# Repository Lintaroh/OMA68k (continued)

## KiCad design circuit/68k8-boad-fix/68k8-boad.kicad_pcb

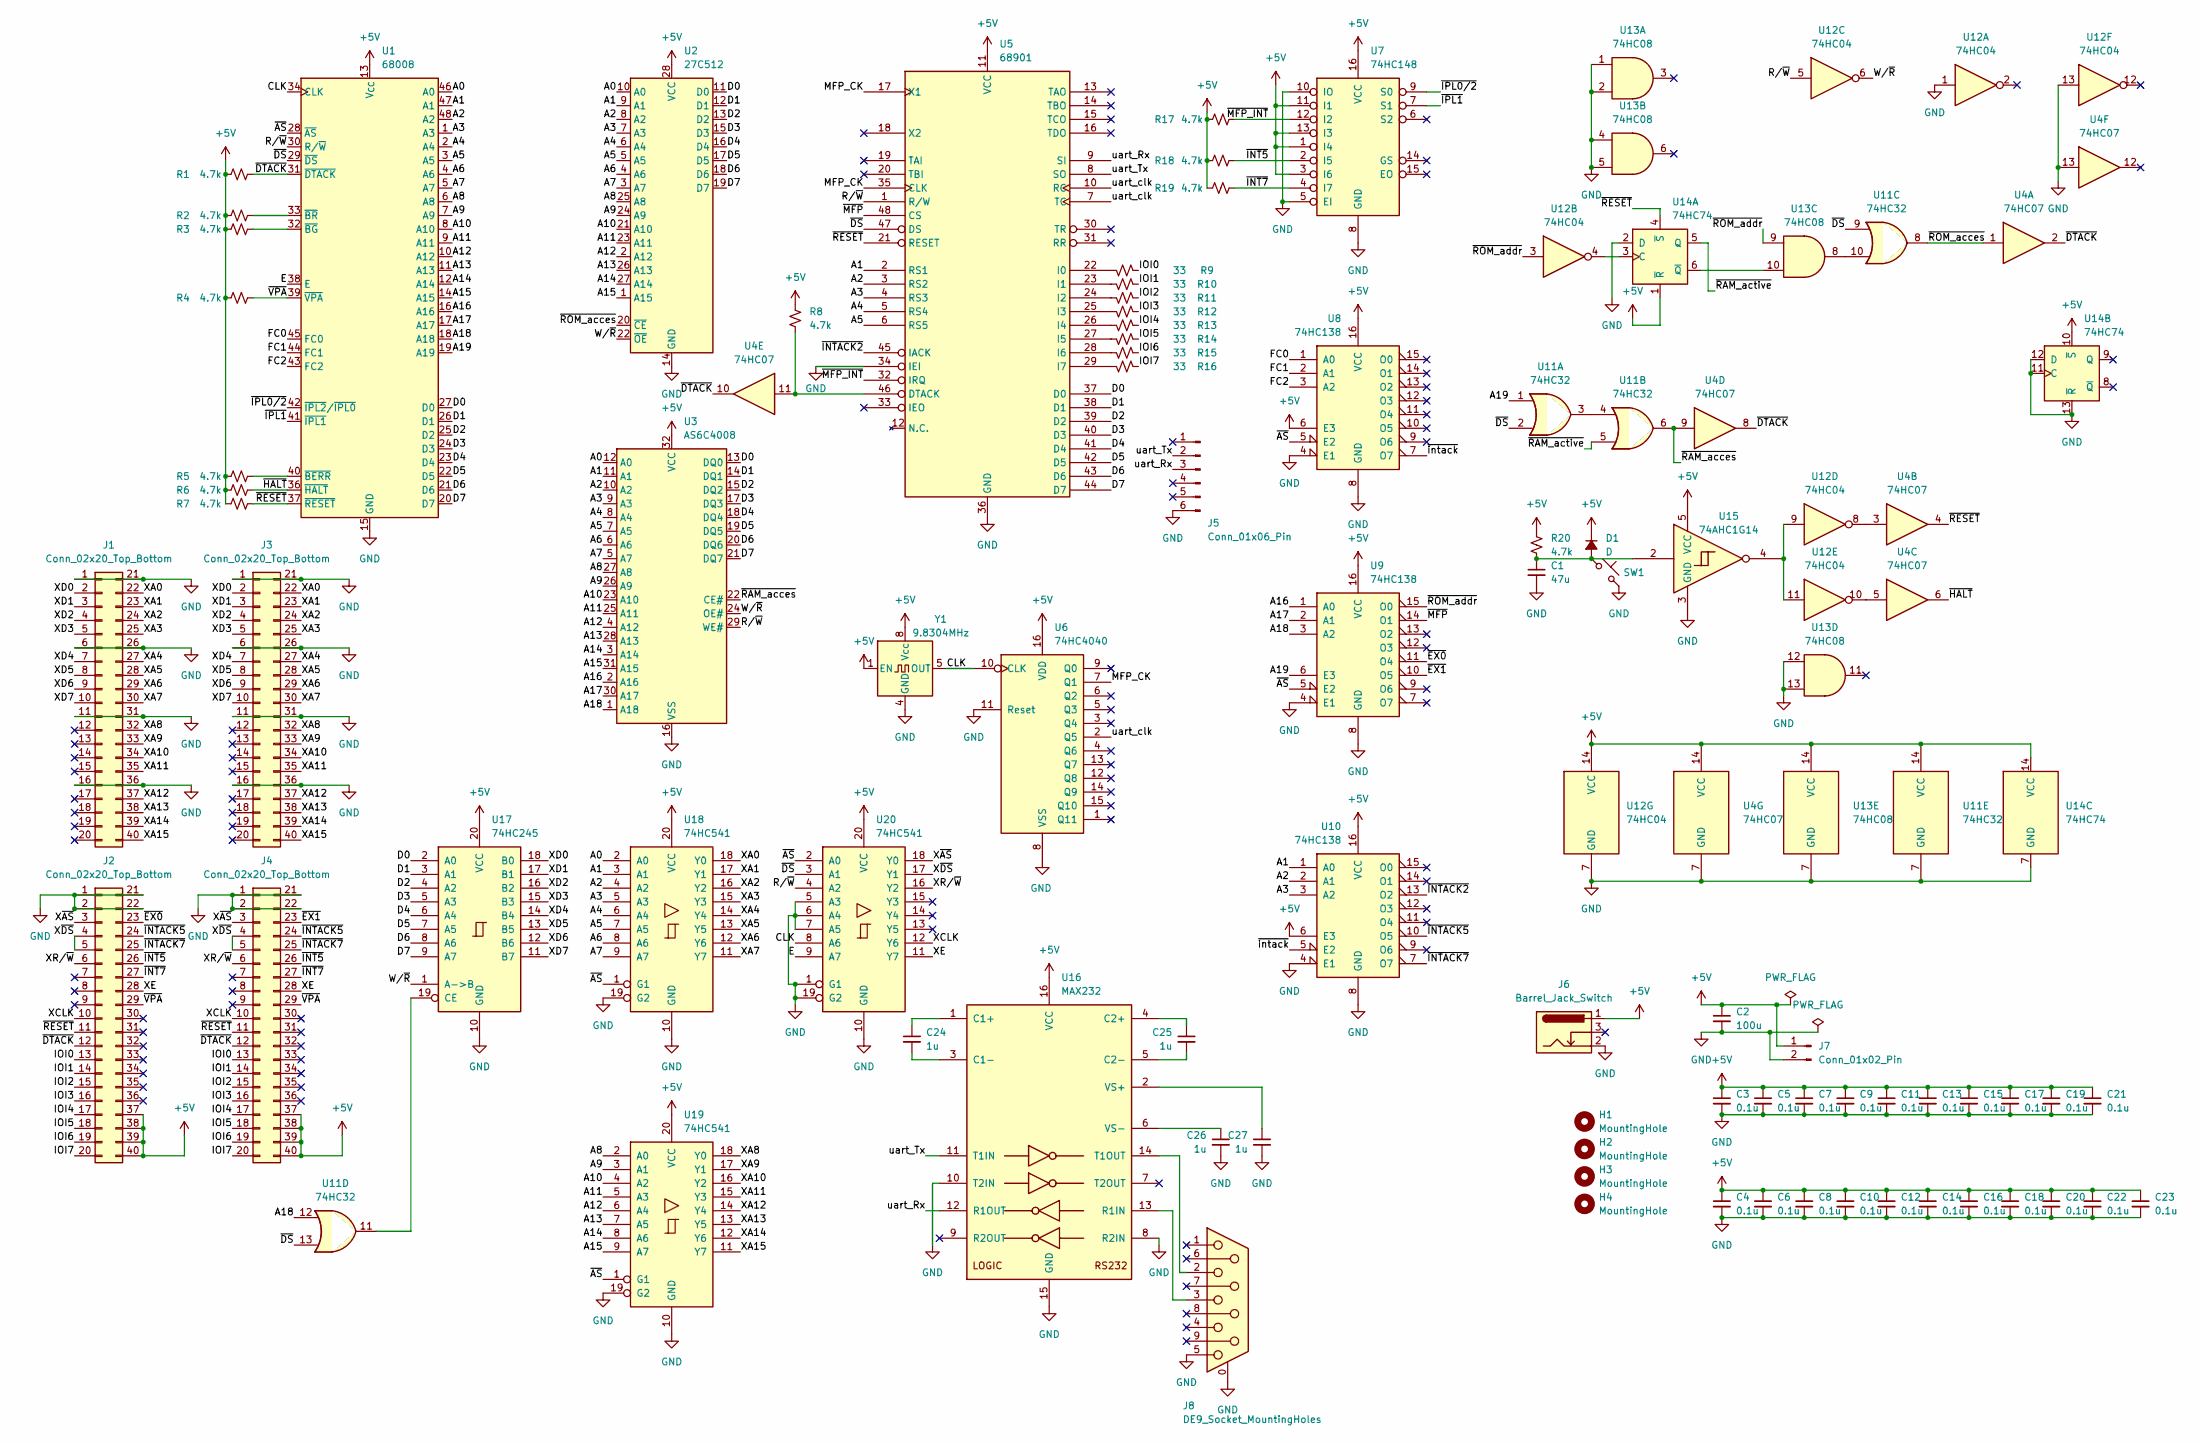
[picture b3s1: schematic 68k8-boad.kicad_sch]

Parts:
C1: 47u; CP_Radial_D5.0mm_P2.50mm
C2: 100u; CP_Radial_D6.3mm_P2.50mm
C3, C4, C5, C6, C7, C8, C9, C10, C11, C12, C13, C14, C15, C16, C17, C18, C19, C20, C21, C22, C23: 0.1u; C_Disc_D4.3mm_W1.9mm_P5.00mm
C24, C25, C26, C27: 1u; C_0805_2012Metric
D1: D; D_DO-34_SOD68_P7.62mm_Horizontal
H1, H2, H3, H4: MountingHole; MountingHole_3.2mm_M3
J1, J2, J3, J4: Conn_02x20_Top_Bottom; PinSocket_2x20_P2.54mm_Vertical
J5: Conn_01x06_Pin; PinHeader_1x06_P2.54mm_Vertical
J6: Barrel_Jack_Switch; BarrelJack_Horizontal
J7: Conn_01x02_Pin; JST_EH_B2B-EH-A_1x02_P2.50mm_Vertical
J8: DE9_Socket_MountingHoles; DSUB-9_Socket_Horizontal_P2.77x2.84mm_EdgePinOffset7.70mm_H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
R1, R2, R3, R4, R5, R6, R7, R8, R17, R18, R19, R20: 4.7k; R_0603_1608Metric
R9, R10, R11, R12, R13, R14, R15, R16: 33; R_0603_1608Metric
SW1: SW_PUSH_6mm_H5mm
U1: 68008; DIP-48_W15.24mm
U2: 27C512; DIP-28_W15.24mm
U3: AS6C4008; DIP-32_W15.24mm
U4: 74HC07; DIP-14_W7.62mm
U5: 68901; DIP-48_W15.24mm
U6: 74HC4040; DIP-16_W7.62mm
U7: 74HC148; DIP-16_W7.62mm
U8, U9, U10: 74HC138; DIP-16_W7.62mm
U11: 74HC32; DIP-14_W7.62mm
U12: 74HC04; DIP-14_W7.62mm
U13: 74HC08; DIP-14_W7.62mm
U14: 74HC74; DIP-14_W7.62mm
U15: 74AHC1G14; SOT-23-5
U16: MAX232; DIP-16_W7.62mm
U17: 74HC245; DIP-20_W7.62mm
U18, U19, U20: 74HC541; DIP-20_W7.62mm
Y1: 9.8304MHz; Oscillator_DIP-8

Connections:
+5V: C2.1, C3.1, C4.1, C5.1, C6.1, C7.1, C8.1, C9.1, C10.1, C11.1, C12.1, C13.1, C14.1, C15.1, C16.1, C17.1, C18.1, C19.1, C20.1, C21.1, C22.1, C23.1, D1.1 (K), J2.37, J2.38, J2.39, J2.40, J4.37, J4.38, J4.39, J4.40, J6.1, J7.1, R1.1, R2.1, R3.1, R4.1, R5.1, R6.1, R7.1, R8.1, R17.1, R18.1, R19.1, R20.1, U1.13 (V_{CC}), U2.28 (VCC), U3.32 (VCC), U4.14 (VCC), U5.11 (VCC), U6.16 (VDD), U7.1 (I4), U7.3 (I6), U7.11 (I1), U7.13 (I3), U7.16 (VCC), U8.6 (E3), U8.16 (VCC), U9.16 (VCC), U10.6 (E3), U10.16 (VCC), U11.14 (VCC), U12.14 (VCC), U13.14 (VCC), U14.1 (~R), U14.10 (~S), U14.14 (VCC), U15.5 (VCC), U16.16 (VCC), U17.20 (VCC), U18.20 (VCC), U19.20 (VCC), U20.20 (VCC), Y1.1 (EN), Y1.8 (Vcc)
/A0: U1.46 (A0), U2.10 (A0), U3.12 (A0), U18.2 (A0)
/A1: U1.47 (A1), U2.9 (A1), U3.11 (A1), U5.2 (RS1), U10.1 (A0), U18.3 (A1)
/A2: U1.48 (A2), U2.8 (A2), U3.10 (A2), U5.3 (RS2), U10.2 (A1), U18.4 (A2)
/A3: U1.1 (A3), U2.7 (A3), U3.9 (A3), U5.4 (RS3), U10.3 (A2), U18.5 (A3)
/A4: U1.2 (A4), U2.6 (A4), U3.8 (A4), U5.5 (RS4), U18.6 (A4)
/A5: U1.3 (A5), U2.5 (A5), U3.7 (A5), U5.6 (RS5), U18.7 (A5)
/A6: U1.4 (A6), U2.4 (A6), U3.6 (A6), U18.8 (A6)
/A7: U1.5 (A7), U2.3 (A7), U3.5 (A7), U18.9 (A7)
/A8: U1.6 (A8), U2.25 (A8), U3.27 (A8), U19.2 (A0)
/A9: U1.7 (A9), U2.24 (A9), U3.26 (A9), U19.3 (A1)
/A10: U1.8 (A10), U2.21 (A10), U3.23 (A10), U19.4 (A2)
/A11: U1.9 (A11), U2.23 (A11), U3.25 (A11), U19.5 (A3)
/A12: U1.10 (A12), U2.2 (A12), U3.4 (A12), U19.6 (A4)
/A13: U1.11 (A13), U2.26 (A13), U3.28 (A13), U19.7 (A5)
/A14: U1.12 (A14), U2.27 (A14), U3.3 (A14), U19.8 (A6)
/A15: U1.14 (A15), U2.1 (A15), U3.31 (A15), U19.9 (A7)
/A16: U1.16 (A16), U3.2 (A16), U9.1 (A0)
/A17: U1.17 (A17), U3.30 (A17), U9.2 (A1)
/A18: U1.18 (A18), U3.1 (A18), U9.3 (A2), U11.12
/A19: U1.19 (A19), U9.6 (E3), U11.1
/CLK: U1.34 (CLK), U6.10 (CLK), U20.8 (A6), Y1.5 (OUT)
/D0: U1.27 (D0), U2.11 (D0), U3.13 (DQ0), U5.37 (D0), U17.2 (A0)
/D1: U1.26 (D1), U2.12 (D1), U3.14 (DQ1), U5.38 (D1), U17.3 (A1)
/D2: U1.25 (D2), U2.13 (D2), U3.15 (DQ2), U5.39 (D2), U17.4 (A2)
/D3: U1.24 (D3), U2.15 (D3), U3.17 (DQ3), U5.40 (D3), U17.5 (A3)
/D4: U1.23 (D4), U2.16 (D4), U3.18 (DQ4), U5.41 (D4), U17.6 (A4)
/D5: U1.22 (D5), U2.17 (D5), U3.19 (DQ5), U5.42 (D5), U17.7 (A5)
/D6: U1.21 (D6), U2.18 (D6), U3.20 (DQ6), U5.43 (D6), U17.8 (A6)
/D7: U1.20 (D7), U2.19 (D7), U3.21 (DQ7), U5.44 (D7), U17.9 (A7)
/E: U1.38 (E), U20.9 (A7)
/FC0: U1.45 (FC0), U8.1 (A0)
/FC1: U1.44 (FC1), U8.2 (A1)
/FC2: U1.43 (FC2), U8.3 (A2)
/IOI0: J2.13, J4.13, R9.1
/IOI1: J2.14, J4.14, R10.1
/IOI2: J2.15, J4.15, R11.1
/IOI3: J2.16, J4.16, R12.1
/IOI4: J2.17, J4.17, R13.1
/IOI5: J2.18, J4.18, R14.1
/IOI6: J2.19, J4.19, R15.1
/IOI7: J2.20, J4.20, R16.1
/MFP_CK: U5.17 (X1), U5.35 (CLK), U6.7 (Q1)
/R/~W: U1.30 (R/~W), U3.29 (WE#), U5.1 (R/W), U12.5, U20.4 (A2)
/W/~R: U2.22 (~OE), U3.24 (OE#), U12.6, U17.1 (A->B)
/XA0: J1.22, J3.22, U18.18 (Y0)
/XA1: J1.23, J3.23, U18.17 (Y1)
/XA2: J1.24, J3.24, U18.16 (Y2)
/XA3: J1.25, J3.25, U18.15 (Y3)
/XA4: J1.27, J3.27, U18.14 (Y4)
/XA5: J1.28, J3.28, U18.13 (Y5)
/XA6: J1.29, J3.29, U18.12 (Y6)
/XA7: J1.30, J3.30, U18.11 (Y7)
/XA8: J1.32, J3.32, U19.18 (Y0)
/XA9: J1.33, J3.33, U19.17 (Y1)
/XA10: J1.34, J3.34, U19.16 (Y2)
/XA11: J1.35, J3.35, U19.15 (Y3)
/XA12: J1.37, J3.37, U19.14 (Y4)
/XA13: J1.38, J3.38, U19.13 (Y5)
/XA14: J1.39, J3.39, U19.12 (Y6)
/XA15: J1.40, J3.40, U19.11 (Y7)
/XCLK: J2.10, J4.10, U20.12 (Y6)
/XD0: J1.2, J3.2, U17.18 (B0)
/XD1: J1.3, J3.3, U17.17 (B1)
/XD2: J1.4, J3.4, U17.16 (B2)
/XD3: J1.5, J3.5, U17.15 (B3)
/XD4: J1.7, J3.7, U17.14 (B4)
/XD5: J1.8, J3.8, U17.13 (B5)
/XD6: J1.9, J3.9, U17.12 (B6)
/XD7: J1.10, J3.10, U17.11 (B7)
/XE: J2.28, J4.28, U20.11 (Y7)
/XR/~W: J2.6, J4.6, U20.16 (Y2)
/X~AS: J2.3, J4.3, U20.18 (Y0)
/X~DS: J2.4, J2.5, J4.4, J4.5, U20.17 (Y1)
/uart_Rx: J5.3, U5.9 (SI), U16.12 (R1OUT)
/uart_Tx: J5.2, U5.8 (SO), U16.11 (T1IN)
/uart_clk: U5.7 (TC), U5.10 (RC), U6.2 (Q5)
/~AS: U1.28 (~AS), U8.5 (E2), U9.5 (E2), U18.1 (G1), U19.1 (G1), U20.2 (A0)
/~DS: U1.29 (~DS), U5.47 (DS), U11.2, U11.9, U11.13, U20.3 (A1)
/~DTACK: J2.12, J4.12, R1.2, U1.31 (~DTACK), U4.2, U4.8, U4.10
/~EX0: J2.23, U9.11 (O4)
/~EX1: J4.23, U9.10 (O5)
/~HALT: R6.2, U1.36 (~HALT), U4.6
/~INT5: J2.26, J4.26, R18.2, U7.2 (I5)
/~INT7: J2.27, J4.27, R19.2, U7.4 (I7)
/~INTACK2: U5.45 (IACK), U10.13 (O2)
/~INTACK5: J2.24, J4.24, U10.10 (O5)
/~INTACK7: J2.25, J4.25, U10.7 (O7)
/~IPL0/2: U1.42 (~IPL2/~IPL0), U7.9 (S0)
/~IPL1: U1.41 (~IPL1), U7.7 (S1)
/~MFP_INT: R17.2, U5.32 (IRQ), U7.12 (I2)
/~MFP: U5.48 (CS), U9.14 (O1)
/~RAM_acces: U3.22 (CE#), U4.9, U11.6
/~RAM_active: U11.5, U14.5 (Q)
/~RESET: J2.11, J4.11, R7.2, U1.37 (~RESET), U4.4, U5.21 (RESET), U14.4 (~S)
/~ROM_acces: U2.20 (~CE), U4.1, U11.8
/~ROM_addr: U9.15 (O0), U12.3, U13.9
/~VPA: J2.29, J4.29, R4.2, U1.39 (~VPA)
/~intack: U8.7 (O7), U10.5 (E2)
GND: C1.2, C2.2, C3.2, C4.2, C5.2, C6.2, C7.2, C8.2, C9.2, C10.2, C11.2, C12.2, C13.2, C14.2, C15.2, C16.2, C17.2, C18.2, C19.2, C20.2, C21.2, C22.2, C23.2, C26.2, C27.2, J1.1, J1.6, J1.11, J1.16, J1.21, J1.26, J1.31, J1.36, J2.1, J2.2, J2.21, J2.22, J3.1, J3.6, J3.11, J3.16, J3.21, J3.26, J3.31, J3.36, J4.1, J4.2, J4.21, J4.22, J5.6, J6.2, J7.2, J8.0 (PAD), J8.5, SW1.2, U1.15 (GND), U1.35 (GND), U2.14 (GND), U3.16 (VSS), U4.7 (GND), U4.13, U5.34 (IEI), U5.36 (GND), U6.8 (VSS), U6.11 (Reset), U7.5 (EI), U7.8 (GND), U7.10 (IO), U8.4 (E1), U8.8 (GND), U9.4 (E1), U9.8 (GND), U10.4 (E1), U10.8 (GND), U11.7 (GND), U12.1, U12.7 (GND), U12.13, U13.1, U13.2, U13.4, U13.5, U13.7 (GND), U13.12, U13.13, U14.2 (D), U14.7 (GND), U14.11 (C), U14.12 (D), U14.13 (~R), U15.3 (GND), U16.8 (R2IN), U16.10 (T2IN), U16.15 (GND), U17.10 (GND), U18.10 (GND), U18.19 (G2), U19.10 (GND), U19.19 (G2), U20.1 (G1), U20.5 (A3), U20.6 (A4), U20.7 (A5), U20.10 (GND), U20.19 (G2), Y1.4 (GND)
unnamed: C1.1, D1.2 (A), R20.2, SW1.1, U15.2
unnamed: R5.2, U1.40 (~BERR)
unnamed: R3.2, U1.32 (~BG)
unnamed: R2.2, U1.33 (~BR)
unnamed: R8.2, U4.11, U5.46 (DTACK)
unnamed: R9.2, U5.22 (I0)
unnamed: R10.2, U5.23 (I1)
unnamed: R11.2, U5.24 (I2)
unnamed: R12.2, U5.25 (I3)
unnamed: R13.2, U5.26 (I4)
unnamed: R14.2, U5.27 (I5)
unnamed: R15.2, U5.28 (I6)
unnamed: R16.2, U5.29 (I7)
unnamed: U11.3, U11.4
unnamed: U11.10, U13.8
unnamed: U4.3, U12.8
unnamed: U4.5, U12.10
unnamed: U12.9, U12.11, U15.4
unnamed: U12.4, U14.3 (C)
unnamed: U13.10, U14.6 (~Q)
unnamed: C24.1, U16.1 (C1+)
unnamed: C24.2, U16.3 (C1-)
unnamed: C25.1, U16.4 (C2+)
unnamed: C25.2, U16.5 (C2-)
unnamed: J8.3, U16.13 (R1IN)
unnamed: J8.2, U16.14 (T1OUT)
unnamed: C27.1, U16.2 (VS+)
unnamed: C26.1, U16.6 (VS-)
unnamed: U11.11, U17.19 (CE)

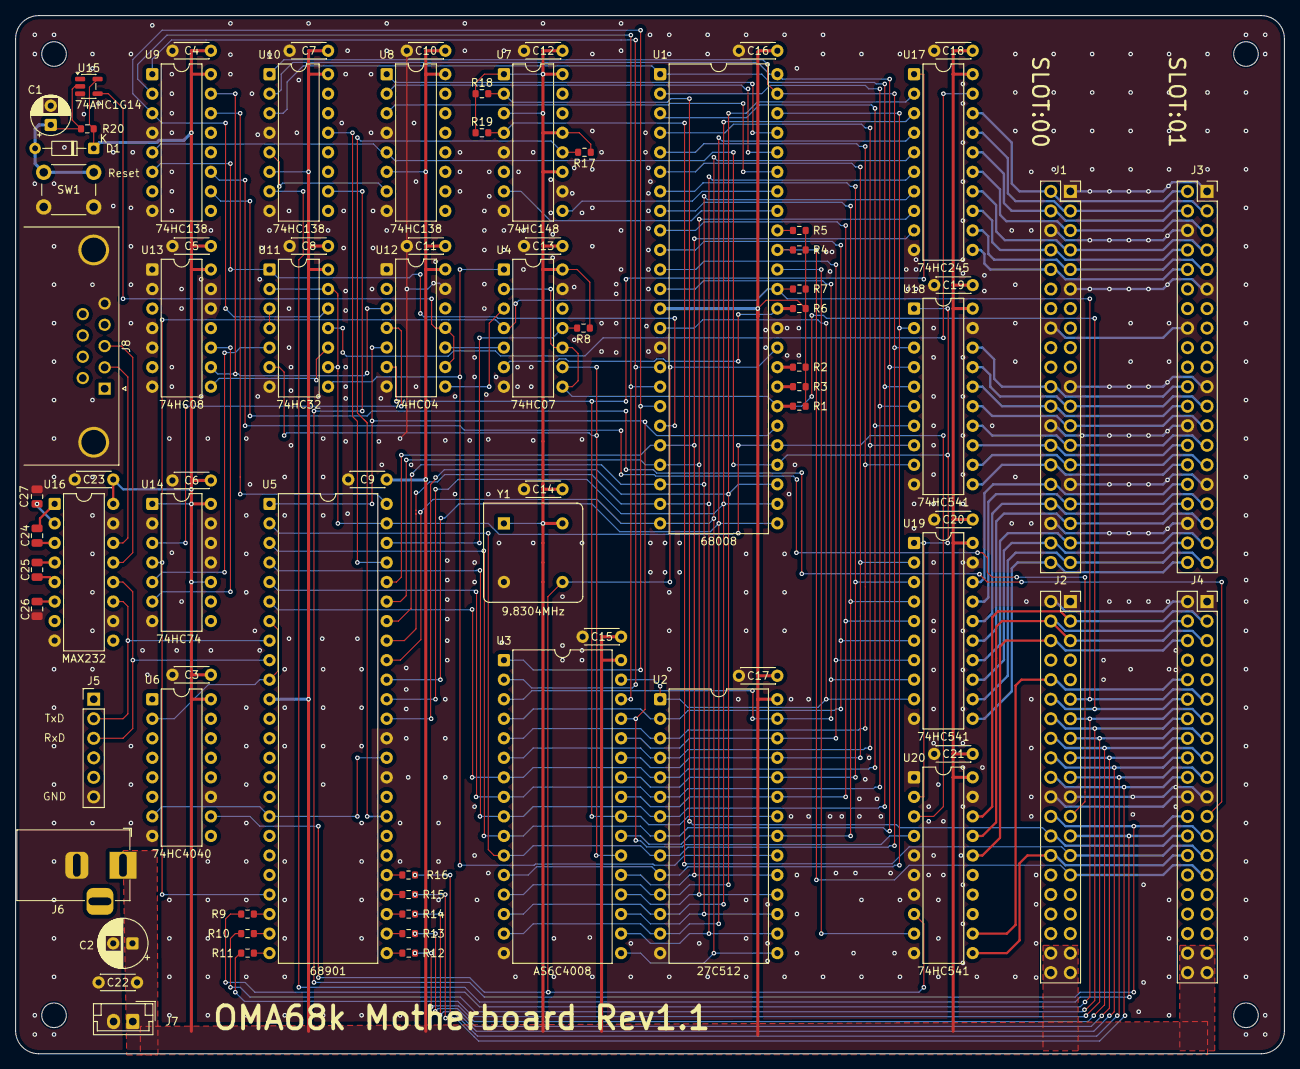
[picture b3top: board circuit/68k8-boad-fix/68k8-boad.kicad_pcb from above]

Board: 2 copper layers, 165.0 x 135.0 mm, 82 parts (0 on the bottom side), 129 nets.

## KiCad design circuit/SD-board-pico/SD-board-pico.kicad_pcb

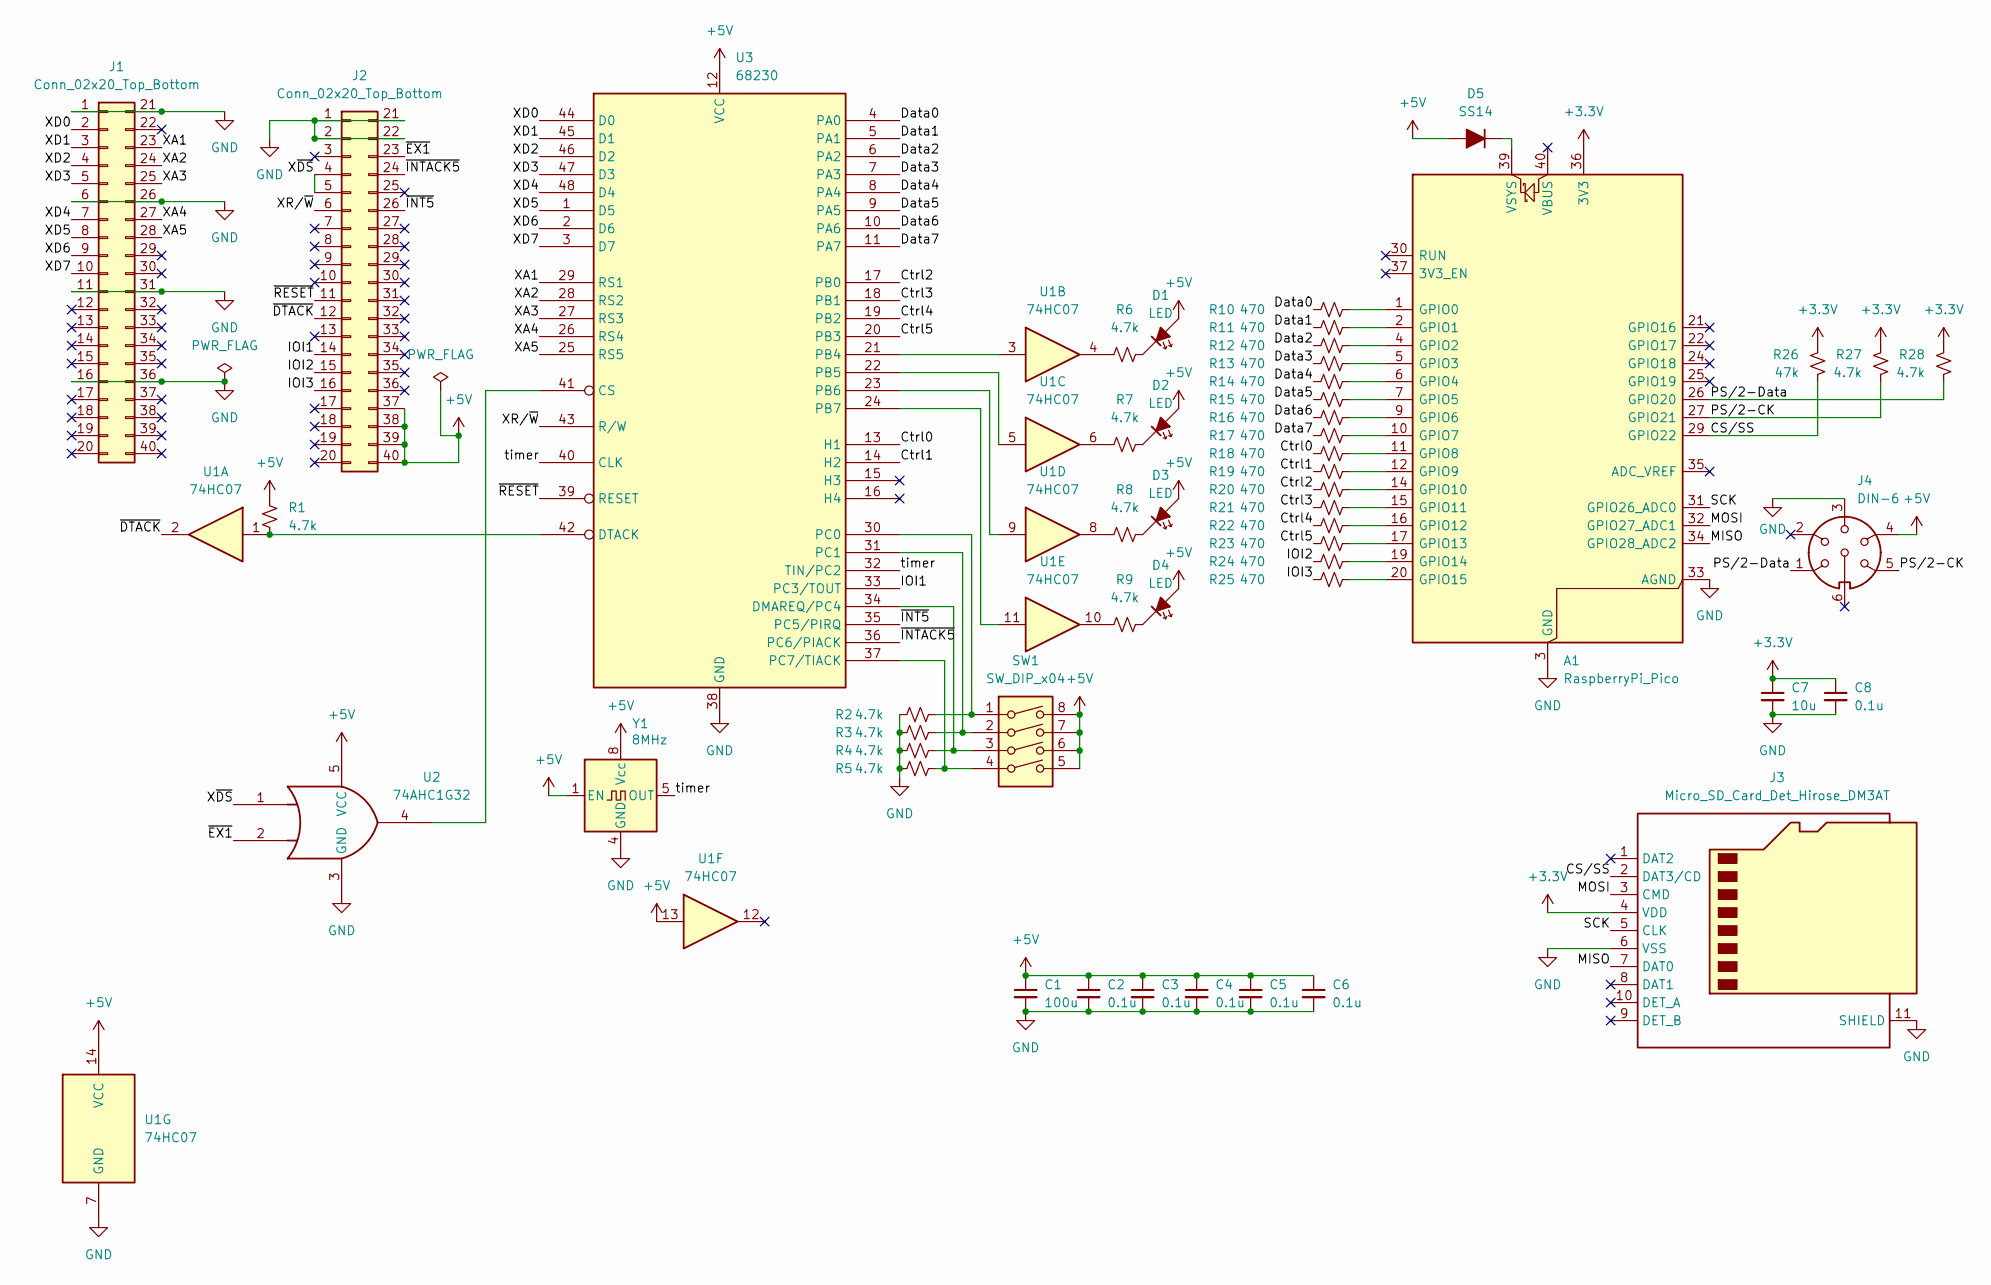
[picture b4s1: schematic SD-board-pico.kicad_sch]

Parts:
A1: RaspberryPi_Pico; RaspberryPi_Pico_Common_Unspecified
C1: 100u; CP_Radial_D6.3mm_P2.50mm
C2, C3, C4, C5, C6, C8: 0.1u; C_Disc_D4.3mm_W1.9mm_P5.00mm
C7: 10u; CP_Radial_D5.0mm_P2.50mm
D1, D2, D3, D4: LED; LED_0603_1608Metric
D5: SS14; D_SMA
J1, J2: Conn_02x20_Top_Bottom; PinHeader_2x20_P2.54mm_Vertical
J3: Micro_SD_Card_Det_Hirose_DM3AT; microSD_HC_Hirose_DM3AT-SF-PEJM5
J4: DIN-6; MiniDIN6-PS_2
R1, R2, R3, R4, R5, R6, R7, R8, R9, R27, R28: 4.7k; R_0603_1608Metric
R10, R11, R12, R13, R14, R15, R16, R17, R18, R19, R20, R21, R22, R23, R24, R25: 470; R_0603_1608Metric
R26: 47k; R_0603_1608Metric
SW1: SW_DIP_x04; SOIC-8_5.3x6.2mm_P1.27mm
U1: 74HC07; DIP-14_W7.62mm
U2: 74AHC1G32; SOT-23-5_HandSoldering
U3: 68230; DIP-48_W15.24mm
Y1: 8MHz; Oscillator_DIP-8

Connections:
+3.3V: A1.36 (3V3), C7.1, C8.1, J3.4 (VDD), R26.1, R27.1, R28.1
+5V: C1.1, C2.1, C3.1, C4.1, C5.1, C6.1, D1.2 (A), D2.2 (A), D3.2 (A), D4.2 (A), D5.2 (A), J2.37, J2.38, J2.39, J2.40, J4.4, R1.1, SW1.5, SW1.6, SW1.7, SW1.8, U1.13, U1.14 (VCC), U2.5 (VCC), U3.12 (VCC), Y1.1 (EN), Y1.8 (Vcc)
/CS/SS: A1.29 (GPIO22), J3.2 (DAT3/CD), R26.2
/Ctrl0: R18.1, U3.13 (H1)
/Ctrl1: R19.1, U3.14 (H2)
/Ctrl2: R20.1, U3.17 (PB0)
/Ctrl3: R21.1, U3.18 (PB1)
/Ctrl4: R22.1, U3.19 (PB2)
/Ctrl5: R23.1, U3.20 (PB3)
/Data0: R10.1, U3.4 (PA0)
/Data1: R11.1, U3.5 (PA1)
/Data2: R12.1, U3.6 (PA2)
/Data3: R13.1, U3.7 (PA3)
/Data4: R14.1, U3.8 (PA4)
/Data5: R15.1, U3.9 (PA5)
/Data6: R16.1, U3.10 (PA6)
/Data7: R17.1, U3.11 (PA7)
/IOI1: J2.14, U3.33 (PC3/TOUT)
/IOI2: J2.15, R24.1
/IOI3: J2.16, R25.1
/MISO: A1.34 (GPIO28_ADC2), J3.7 (DAT0)
/MOSI: A1.32 (GPIO27_ADC1), J3.3 (CMD)
/PS/2-CK: A1.27 (GPIO21), J4.5, R27.2
/PS/2-Data: A1.26 (GPIO20), J4.1, R28.2
/SCK: A1.31 (GPIO26_ADC0), J3.5 (CLK)
/XA1: J1.23, U3.29 (RS1)
/XA2: J1.24, U3.28 (RS2)
/XA3: J1.25, U3.27 (RS3)
/XA4: J1.27, U3.26 (RS4)
/XA5: J1.28, U3.25 (RS5)
/XD0: J1.2, U3.44 (D0)
/XD1: J1.3, U3.45 (D1)
/XD2: J1.4, U3.46 (D2)
/XD3: J1.5, U3.47 (D3)
/XD4: J1.7, U3.48 (D4)
/XD5: J1.8, U3.1 (D5)
/XD6: J1.9, U3.2 (D6)
/XD7: J1.10, U3.3 (D7)
/XR/~W: J2.6, U3.43 (R/W)
/X~DS: J2.4, J2.5, U2.1
/timer: U3.32 (TIN/PC2), U3.40 (CLK), Y1.5 (OUT)
/~DTACK: J2.12, U1.2
/~EX1: J2.23, U2.2
/~INT5: J2.26, U3.35 (PC5/PIRQ)
/~INTACK5: J2.24, U3.36 (PC6/PIACK)
/~RESET: J2.11, U3.39 (RESET)
GND: A1.3 (GND), A1.8 (GND), A1.13 (GND), A1.18 (GND), A1.23 (GND), A1.28 (GND), A1.33 (AGND), A1.38 (GND), C1.2, C2.2, C3.2, C4.2, C5.2, C6.2, C7.2, C8.2, J1.1, J1.6, J1.11, J1.16, J1.21, J1.26, J1.31, J1.36, J2.1, J2.2, J2.21, J2.22, J3.6 (VSS), J3.11 (SHIELD), J4.3, R2.1, R3.1, R4.1, R5.1, U1.7 (GND), U2.3 (GND), U3.38 (GND), Y1.4 (GND)
unnamed: A1.1 (GPIO0), R10.2
unnamed: A1.2 (GPIO1), R11.2
unnamed: A1.4 (GPIO2), R12.2
unnamed: A1.5 (GPIO3), R13.2
unnamed: A1.6 (GPIO4), R14.2
unnamed: A1.7 (GPIO5), R15.2
unnamed: A1.9 (GPIO6), R16.2
unnamed: A1.10 (GPIO7), R17.2
unnamed: A1.11 (GPIO8), R18.2
unnamed: A1.12 (GPIO9), R19.2
unnamed: A1.14 (GPIO10), R20.2
unnamed: A1.15 (GPIO11), R21.2
unnamed: A1.16 (GPIO12), R22.2
unnamed: A1.17 (GPIO13), R23.2
unnamed: A1.19 (GPIO14), R24.2
unnamed: A1.20 (GPIO15), R25.2
unnamed: A1.39 (VSYS), D5.1 (K)
unnamed: D1.1 (K), R6.2
unnamed: D2.1 (K), R7.2
unnamed: D3.1 (K), R8.2
unnamed: D4.1 (K), R9.2
unnamed: R6.1, U1.4
unnamed: R7.1, U1.6
unnamed: R8.1, U1.8
unnamed: R9.1, U1.10
unnamed: U2.4, U3.41 (CS)
unnamed: R4.2, SW1.3, U3.34 (DMAREQ/PC4)
unnamed: R1.2, U1.1, U3.42 (DTACK)
unnamed: U1.3, U3.21 (PB4)
unnamed: U1.5, U3.22 (PB5)
unnamed: U1.9, U3.23 (PB6)
unnamed: U1.11, U3.24 (PB7)
unnamed: R2.2, SW1.1, U3.30 (PC0)
unnamed: R3.2, SW1.2, U3.31 (PC1)
unnamed: R5.2, SW1.4, U3.37 (PC7/TIACK)

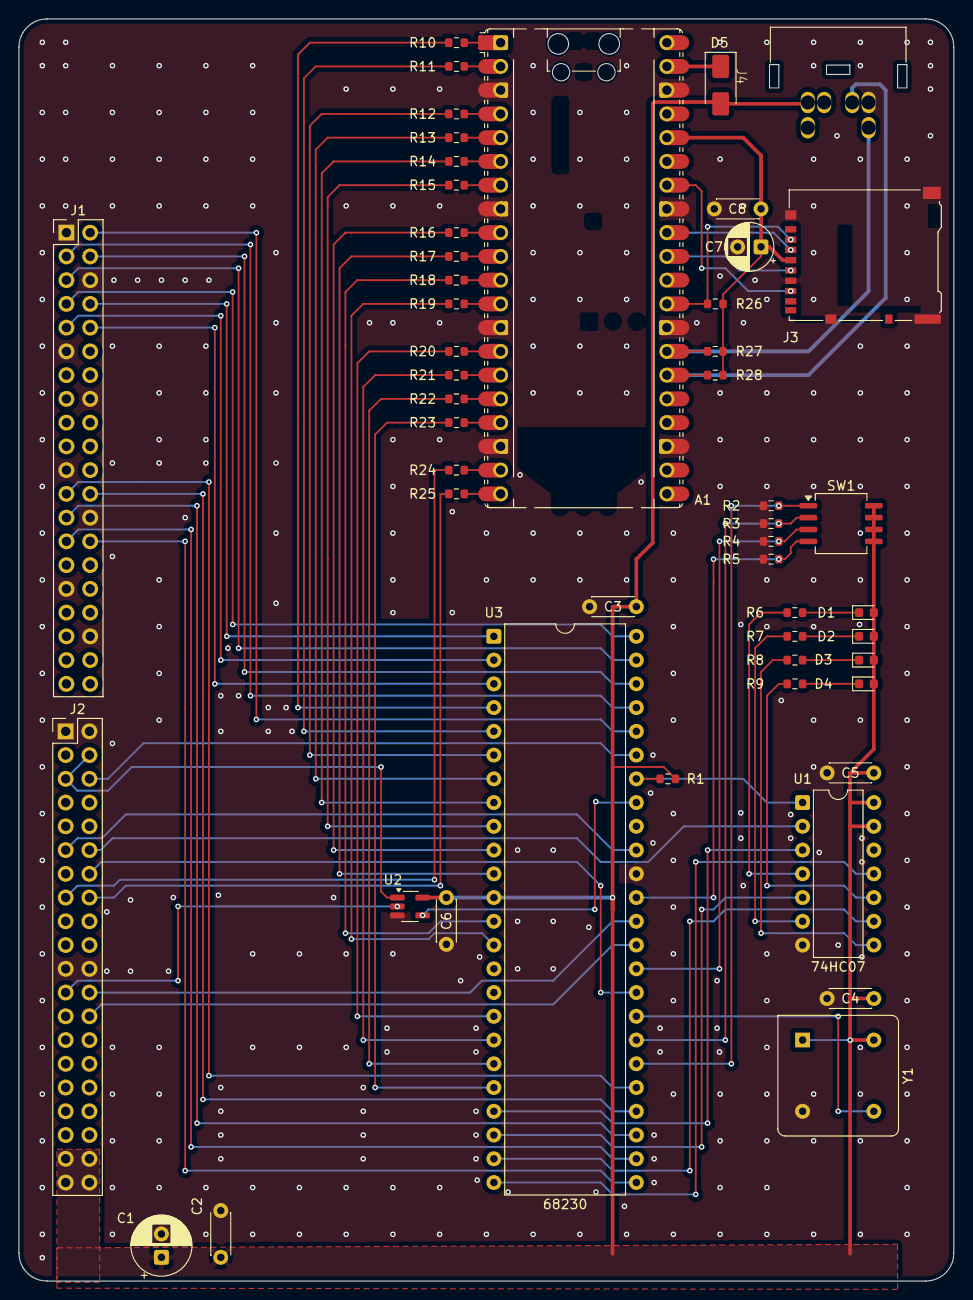
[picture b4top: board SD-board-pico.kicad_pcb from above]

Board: 2 copper layers, 100.0 x 135.0 mm, 51 parts (0 on the bottom side), 82 nets.

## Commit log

2026-05-15 init
